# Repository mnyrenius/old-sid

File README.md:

# old-sid
Old project using MOS6581/8580

PCB design + software.

## Schematics

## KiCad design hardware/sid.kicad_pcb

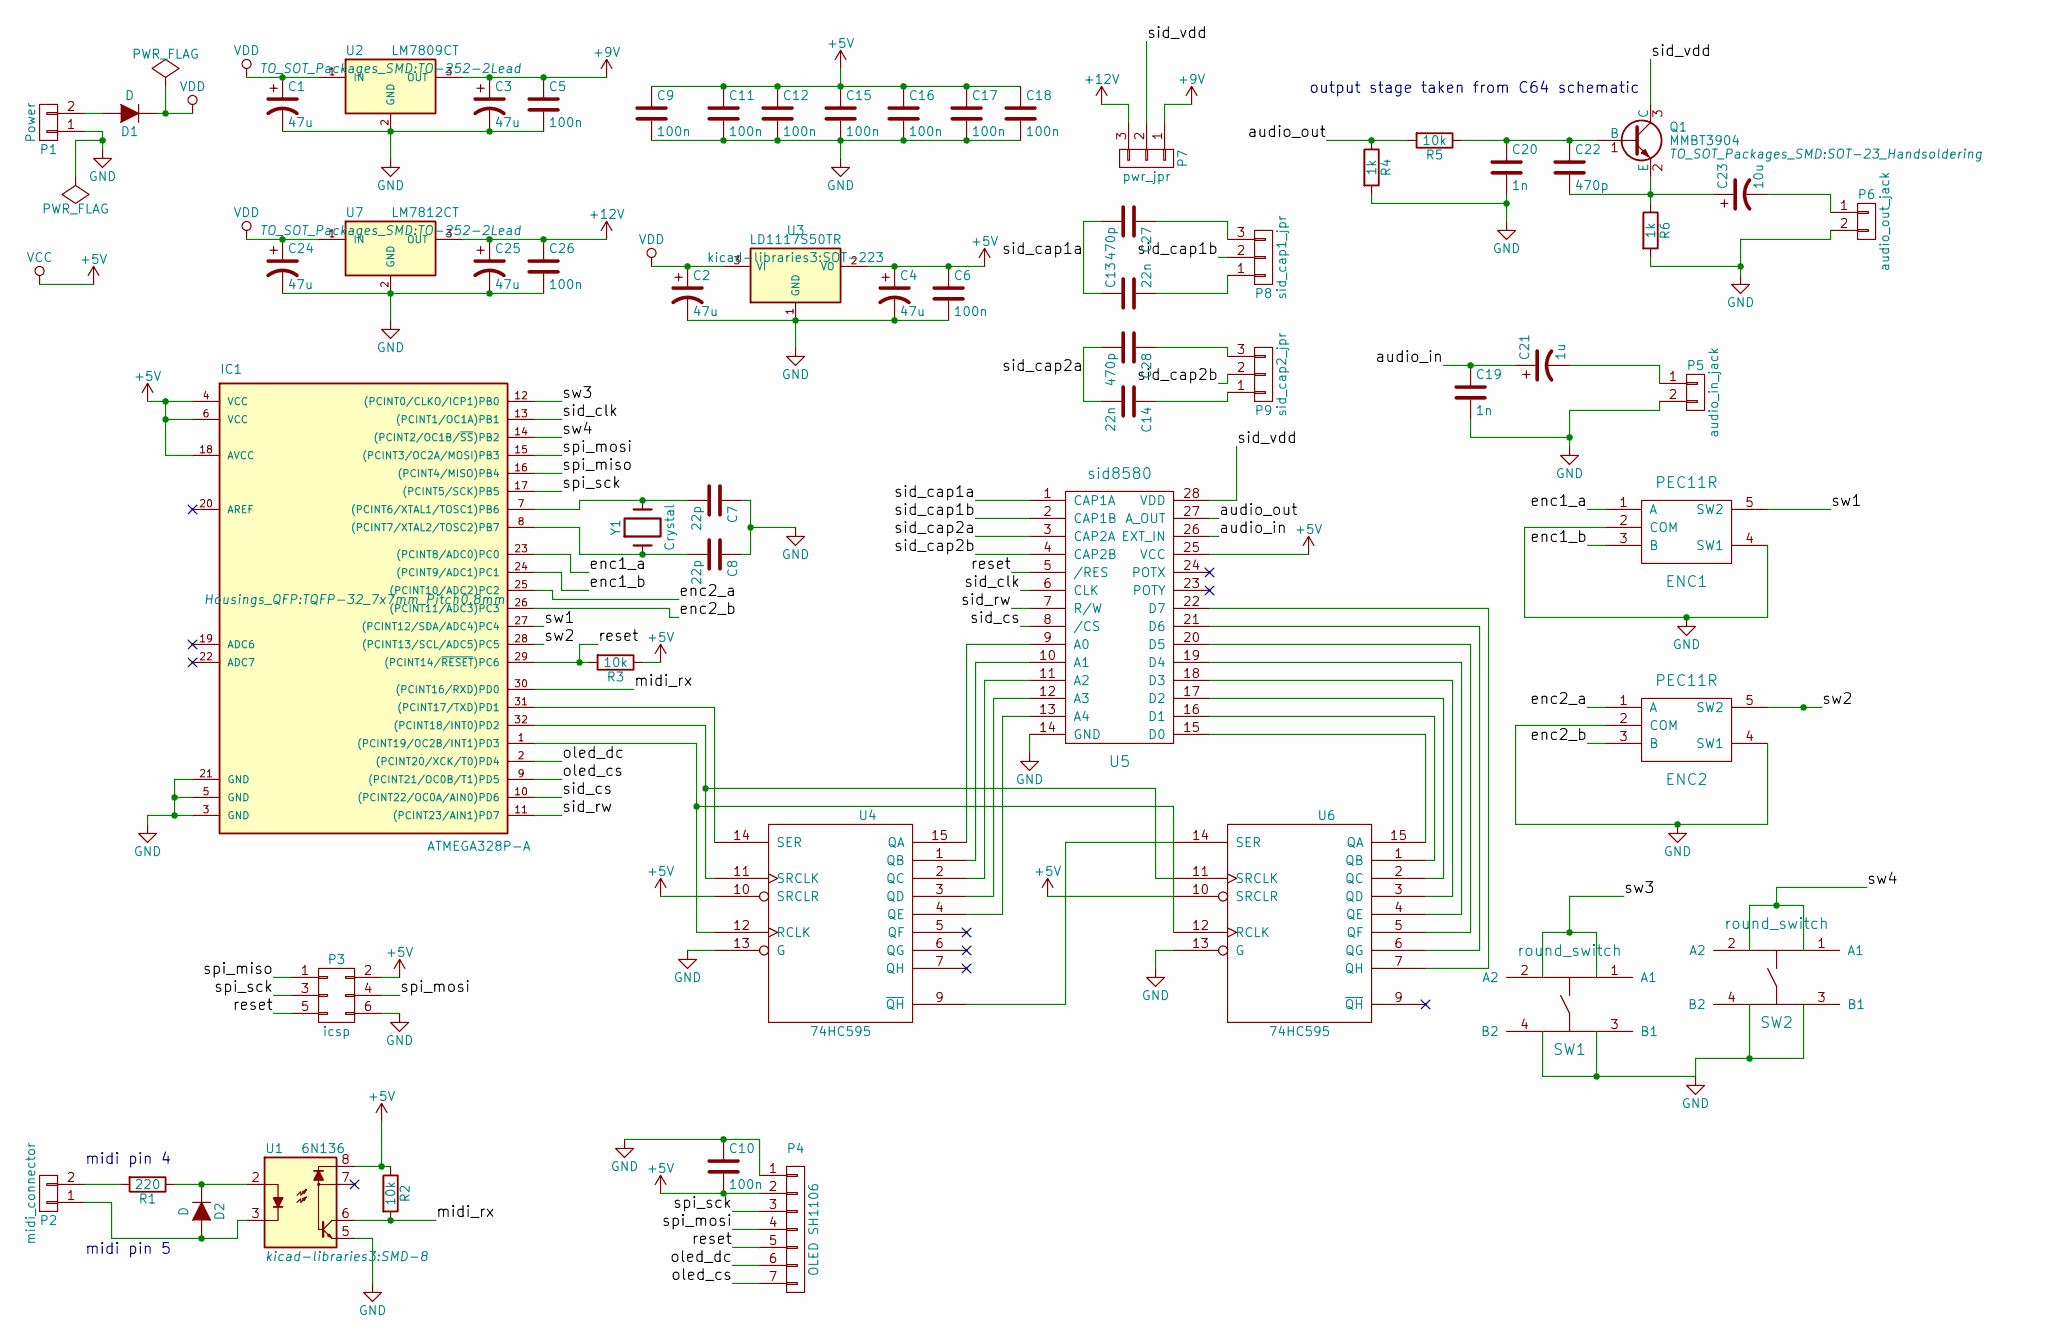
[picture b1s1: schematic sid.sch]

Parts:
C1, C2, C3, C4, C24, C25: 47u; c_elec_4x5.3
C5, C6, C9, C10, C11, C12, C15, C16, C17, C18, C26: 100n; C_0603_HandSoldering
C7, C8: 22p; C_0603_HandSoldering
C13, C14: 22n; C_0603_HandSoldering
C19, C20: 1n; C_0603_HandSoldering
C21: 1u; c_elec_4x5.3
C22, C27, C28: 470p; C_0603_HandSoldering
C23: 10u; c_elec_4x5.3
D1: D; SOD123
D2: D; SOD-323
ENC1, ENC2: PEC11R
IC1: ATMEGA328P-A; TQFP-32_7x7mm_Pitch0.8mm
P1: Power; Pin_Header_Straight_1x02
P2: midi_connector; Pin_Header_Straight_1x02
P3: icsp; Pin_Header_Straight_2x03
P4: OLED SH1106; OLED_SH1106
P5: audio_in_jack; Pin_Header_Straight_1x02
P6: audio_out_jack; Pin_Header_Straight_1x02
P7: pwr_jpr; Pin_Header_Straight_1x03
P8: sid_cap1_jpr; Pin_Header_Straight_1x03
P9: sid_cap2_jpr; Pin_Header_Straight_1x03
Q1: MMBT3904; SOT-23_Handsoldering
R1: 220; R_0603_HandSoldering
R2, R3, R5: 10k; R_0603_HandSoldering
R4, R6: 1k; R_0603_HandSoldering
SW1, SW2: round_switch; SWITCH_CK
U1: 6N136; SMD-8
U2: LM7809CT; TO-252-2Lead
U3: LD1117S50TR; SOT-223
U4, U6: 74HC595; SOIC-16_3.9x9.9mm_Pitch1.27mm
U5: sid8580; DIP-28_W15.24mm_LongPads
U7: LM7812CT; TO-252-2Lead
Y1: Crystal; Crystal_HC49-SD_SMD

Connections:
+5V: C4.1, C6.1, C9.1, C10.2, C11.1, C12.1, C15.1, C16.1, C17.1, C18.1, IC1.4 (VCC), IC1.6 (VCC), IC1.18 (AVCC), P3.2, P4.2, R2.1, R3.1, U1.8, U3.2 (VO), U4.10 (SRCLR), U4.16 (VCC), U5.25 (VCC), U6.10 (SRCLR), U6.16 (VCC)
+9V: C3.1, C5.1, P7.1, U2.3 (OUT)
+12V: C25.1, C26.1, P7.3, U7.3 (OUT)
/audio_in: C19.1, C21.1, U5.26 (EXT_IN)
/audio_out: R4.1, R5.2, U5.27 (A_OUT)
/enc1_a: ENC1.1 (A), IC1.23 ((PCINT8/ADC0)PC0)
/enc1_b: ENC1.3 (B), IC1.24 ((PCINT9/ADC1)PC1)
/enc2_a: ENC2.1 (A), IC1.25 ((PCINT10/ADC2)PC2)
/enc2_b: ENC2.3 (B), IC1.26 ((PCINT11/ADC3)PC3)
/midi_rx: IC1.30 ((PCINT16/RXD)PD0), R2.2, U1.6
/oled_cs: IC1.9 ((PCINT21/OC0B/T1)PD5), P4.7
/oled_dc: IC1.2 ((PCINT20/XCK/T0)PD4), P4.6
/reset: IC1.29 ((PCINT14/~RESET~)PC6), P3.5, P4.5, R3.2, U5.5 (/RES)
/sid_cap1a: C13.1, C27.2, U5.1 (CAP1A)
/sid_cap1b: P8.2, U5.2 (CAP1B)
/sid_cap2a: C14.2, C28.2, U5.3 (CAP2A)
/sid_cap2b: P9.2, U5.4 (CAP2B)
/sid_clk: IC1.13 ((PCINT1/OC1A)PB1), U5.6 (CLK)
/sid_cs: IC1.10 ((PCINT22/OC0A/AIN0)PD6), U5.8 (/CS)
/sid_rw: IC1.11 ((PCINT23/AIN1)PD7), U5.7 (R/W)
/sid_vdd: P7.2, Q1.3 (C), U5.28 (VDD)
/spi_miso: IC1.16 ((PCINT4/MISO)PB4), P3.1
/spi_mosi: IC1.15 ((PCINT3/OC2A/MOSI)PB3), P3.4, P4.4
/spi_sck: IC1.17 ((PCINT5/SCK)PB5), P3.3, P4.3
/sw1: ENC1.5 (SW2), IC1.27 ((PCINT12/SDA/ADC4)PC4)
/sw2: ENC2.5 (SW2), IC1.28 ((PCINT13/SCL/ADC5)PC5)
/sw3: IC1.12 ((PCINT0/CLKO/ICP1)PB0), SW1.1 (A1), SW1.2 (A2)
/sw4: IC1.14 ((PCINT2/OC1B/~SS~)PB2), SW2.1 (A1), SW2.2 (A2)
GND: C1.2, C2.2, C3.2, C4.2, C5.2, C6.2, C7.1, C8.1, C9.2, C10.1, C11.2, C12.2, C15.2, C16.2, C17.2, C18.2, C19.2, C20.2, C24.2, C25.2, C26.2, ENC1.2 (COM), ENC1.4 (SW1), ENC2.2 (COM), ENC2.4 (SW1), IC1.3 (GND), IC1.5 (GND), IC1.21 (GND), P1.1, P3.6, P4.1, P5.2, P6.2, R4.2, R6.2, SW1.3 (B1), SW1.4 (B2), SW2.3 (B1), SW2.4 (B2), U1.5, U2.2 (GND), U3.1 (GND), U4.8 (GND), U4.13 (G), U5.14 (GND), U6.8 (GND), U6.13 (G), U7.2 (GND)
unnamed: C7.2, IC1.7 ((PCINT6/XTAL1/TOSC1)PB6), Y1.2
unnamed: C8.2, IC1.8 ((PCINT7/XTAL2/TOSC2)PB7), Y1.1
unnamed: C13.2, P8.1
unnamed: C14.1, P9.1
unnamed: C20.1, C22.1, Q1.1 (B), R5.1
unnamed: C21.2, P5.1
unnamed: C22.2, C23.1, Q1.2 (E), R6.1
unnamed: C23.2, P6.1
unnamed: C27.1, P8.3
unnamed: C28.1, P9.3
unnamed: D1.2 (A), P1.2
unnamed: D2.1 (K), R1.1, U1.2
unnamed: D2.2 (A), P2.1, U1.3
unnamed: IC1.1 ((PCINT19/OC2B/INT1)PD3), U4.12 (RCLK), U6.12 (RCLK)
unnamed: IC1.31 ((PCINT17/TXD)PD1), U4.14 (SER)
unnamed: IC1.32 ((PCINT18/INT0)PD2), U4.11 (SRCLK), U6.11 (SRCLK)
unnamed: P2.2, R1.2
unnamed: U4.1 (QB), U5.10 (A1)
unnamed: U4.2 (QC), U5.11 (A2)
unnamed: U4.3 (QD), U5.12 (A3)
unnamed: U4.4 (QE), U5.13 (A4)
unnamed: U4.9 (~QH), U6.14 (SER)
unnamed: U4.15 (QA), U5.9 (A0)
unnamed: U5.15 (D0), U6.15 (QA)
unnamed: U5.16 (D1), U6.1 (QB)
unnamed: U5.17 (D2), U6.2 (QC)
unnamed: U5.18 (D3), U6.3 (QD)
unnamed: U5.19 (D4), U6.4 (QE)
unnamed: U5.20 (D5), U6.5 (QF)
unnamed: U5.21 (D6), U6.6 (QG)
unnamed: U5.22 (D7), U6.7 (QH)
VDD: C1.1, C2.1, C24.1, D1.1 (K), U2.1 (IN), U3.3 (VI), U7.1 (IN)

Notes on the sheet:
midi pin 4
midi pin 5
output stage taken from C64 schematic

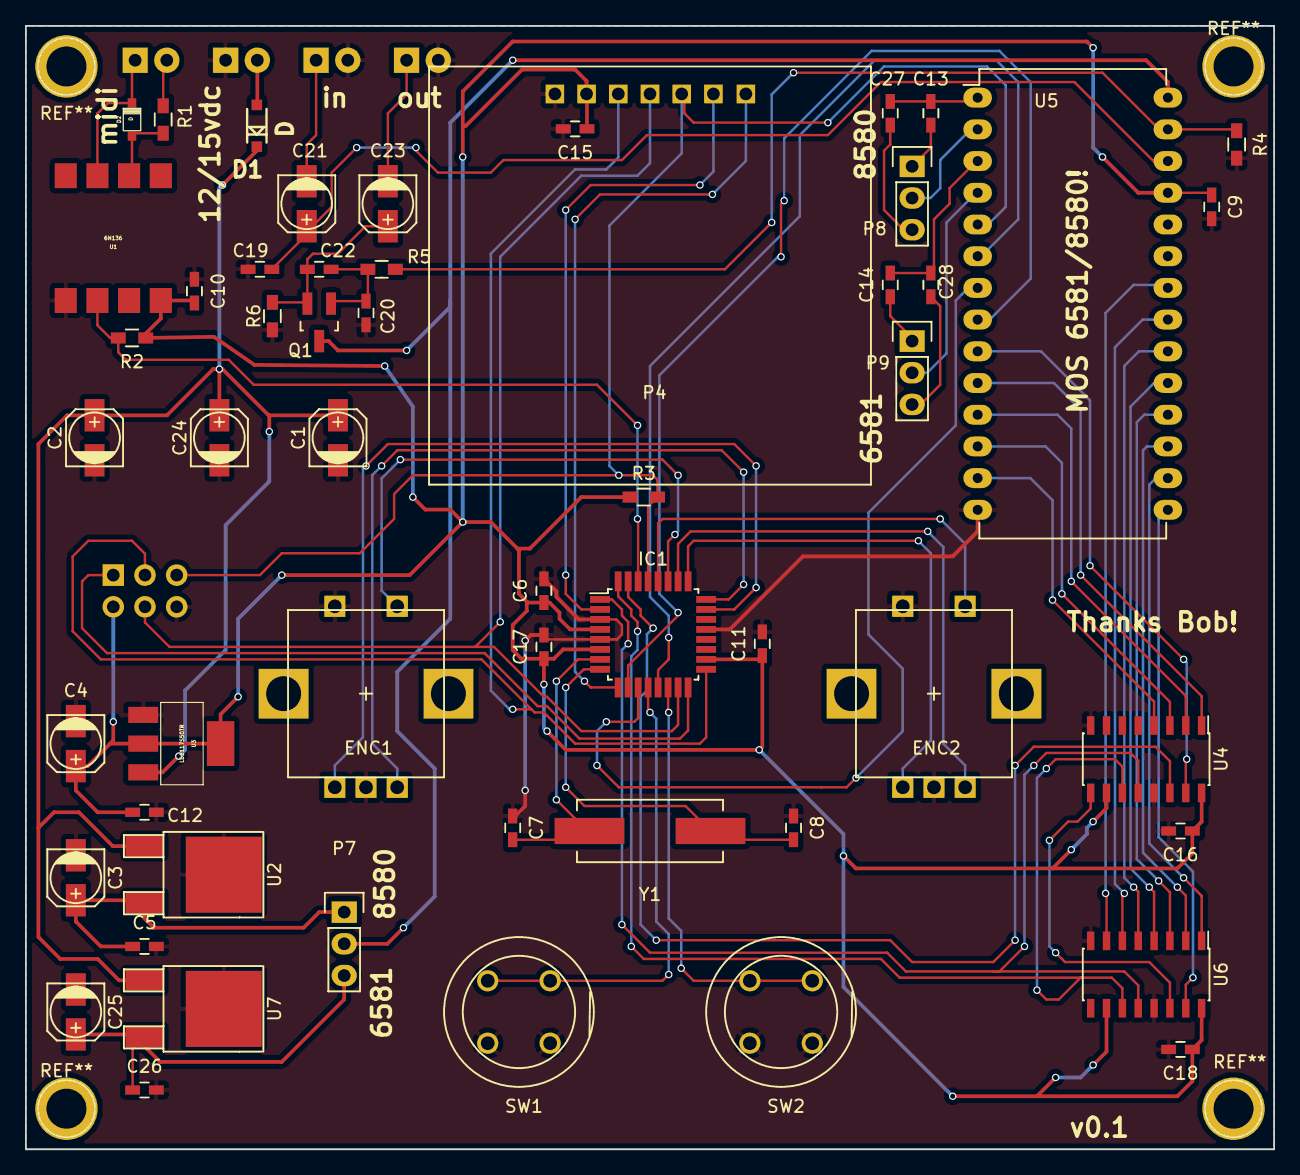
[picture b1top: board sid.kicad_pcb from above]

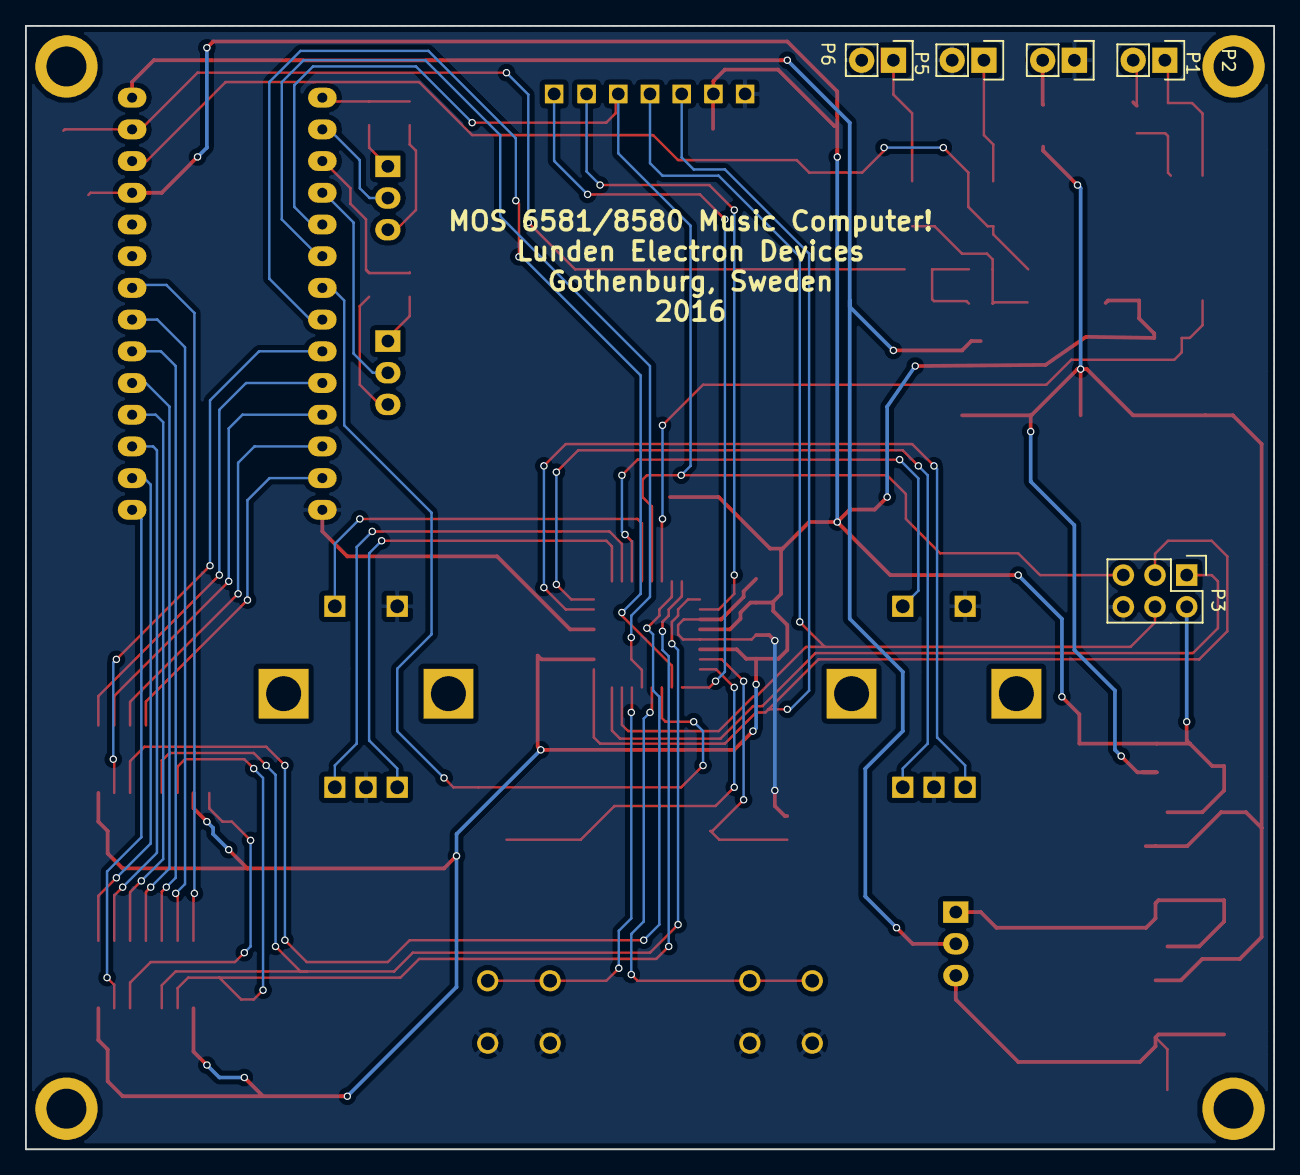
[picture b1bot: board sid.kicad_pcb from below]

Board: 2 copper layers, 100.0 x 90.0 mm, 59 parts (5 on the bottom side), 61 nets.

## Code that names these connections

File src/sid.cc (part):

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 *
 * ------------------------------------ */

const uint8_t midi_rx     = PD0;
const uint8_t hc595_data  = PD1;
const uint8_t hc595_clk   = PD2;
const uint8_t hc595_latch = PD3;

const uint8_t sid_clk     = PB1;
const uint8_t sid_cs      = PD6;
const uint8_t sid_rw      = PD7;
 
const uint8_t spi_mosi    = PB3;
const uint8_t spi_miso    = PB4;
const uint8_t spi_clk     = PB5; 
const uint8_t spi_ss      = PB2; 

const uint8_t enc1_a      = PC0;
const uint8_t enc1_b      = PC1;
const uint8_t enc2_a      = PC2;
const uint8_t enc2_b      = PC3;
const uint8_t sw1         = PC4;
const uint8_t sw2         = PC5;
const uint8_t sw3         = PB0;

const uint16_t notes[] PROGMEM = 
{
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
Menu menu (& voice1_items[0], & render_item, strings::mark);

Encoder _e1 (DDRC, PORTC, PINC, enc1_a, enc1_b, sw1);
Encoder _e2 (DDRC, PORTC, PINC, enc2_a, enc2_b, sw2);
Ui _ui (_e1, _e2, menu, _oled, _settings);
Uart _serial;
Midi<MidiHandler> _midi (_serial); 
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       |  _BV (spi_clk)
       |  _BV (spi_ss)
       |  _BV (sid_clk)
       |  _BV (PD0);

  bit::set (PORTB, sw3);

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
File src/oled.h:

#ifndef _OLED_H_
#define _OLED_H_

#include "avr_types.h"
#include <string.h>
#include <stdlib.h>
#include <avr/pgmspace.h>

const uint8_t ASCII[][5] PROGMEM = 
{
  { 0x00, 0x00, 0x00, 0x00, 0x00 } // 20   (space)
  ,{ 0x00, 0x00, 0x5f, 0x00, 0x00 } // 21 !
  ,{ 0x00, 0x07, 0x00, 0x07, 0x00 } // 22 "
  ,{ 0x14, 0x7f, 0x14, 0x7f, 0x14 } // 23 #
  ,{ 0x24, 0x2a, 0x7f, 0x2a, 0x12 } // 24 $
  ,{ 0x23, 0x13, 0x08, 0x64, 0x62 } // 25 %
  ,{ 0x36, 0x49, 0x55, 0x22, 0x50 } // 26 &
  ,{ 0x00, 0x05, 0x03, 0x00, 0x00 } // 27 '
  ,{ 0x00, 0x1c, 0x22, 0x41, 0x00 } // 28 (
  ,{ 0x00, 0x41, 0x22, 0x1c, 0x00 } // 29 )
  ,{ 0x14, 0x08, 0x3e, 0x08, 0x14 } // 2a *
  ,{ 0x08, 0x08, 0x3e, 0x08, 0x08 } // 2b +
  ,{ 0x00, 0x50, 0x30, 0x00, 0x00 } // 2c ,
  ,{ 0x08, 0x08, 0x08, 0x08, 0x08 } // 2d -
  ,{ 0x00, 0x60, 0x60, 0x00, 0x00 } // 2e .
  ,{ 0x20, 0x10, 0x08, 0x04, 0x02 } // 2f /
  ,{ 0x3e, 0x51, 0x49, 0x45, 0x3e } // 30 0
  ,{ 0x00, 0x42, 0x7f, 0x40, 0x00 } // 31 1
  ,{ 0x42, 0x61, 0x51, 0x49, 0x46 } // 32 2
  ,{ 0x21, 0x41, 0x45, 0x4b, 0x31 } // 33 3
  ,{ 0x18, 0x14, 0x12, 0x7f, 0x10 } // 34 4
  ,{ 0x27, 0x45, 0x45, 0x45, 0x39 } // 35 5
  ,{ 0x3c, 0x4a, 0x49, 0x49, 0x30 } // 36 6
  ,{ 0x01, 0x71, 0x09, 0x05, 0x03 } // 37 7
  ,{ 0x36, 0x49, 0x49, 0x49, 0x36 } // 38 8
  ,{ 0x06, 0x49, 0x49, 0x29, 0x1e } // 39 9
  ,{ 0x00, 0x36, 0x36, 0x00, 0x00 } // 3a :
  ,{ 0x00, 0x56, 0x36, 0x00, 0x00 } // 3b ;
  ,{ 0x08, 0x14, 0x22, 0x41, 0x00 } // 3c <
  ,{ 0x14, 0x14, 0x14, 0x14, 0x14 } // 3d =
  ,{ 0x00, 0x41, 0x22, 0x14, 0x08 } // 3e >
  ,{ 0x02, 0x01, 0x51, 0x09, 0x06 } // 3f ?
  ,{ 0x32, 0x49, 0x79, 0x41, 0x3e } // 40 @
  ,{ 0x7e, 0x11, 0x11, 0x11, 0x7e } // 41 A
  ,{ 0x7f, 0x49, 0x49, 0x49, 0x36 } // 42 B
  ,{ 0x3e, 0x41, 0x41, 0x41, 0x22 } // 43 C
  ,{ 0x7f, 0x41, 0x41, 0x22, 0x1c } // 44 D
  ,{ 0x7f, 0x49, 0x49, 0x49, 0x41 } // 45 E
  ,{ 0x7f, 0x09, 0x09, 0x09, 0x01 } // 46 F
  ,{ 0x3e, 0x41, 0x49, 0x49, 0x7a } // 47 G
  ,{ 0x7f, 0x08, 0x08, 0x08, 0x7f } // 48 H
  ,{ 0x00, 0x41, 0x7f, 0x41, 0x00 } // 49 I
  ,{ 0x20, 0x40, 0x41, 0x3f, 0x01 } // 4a J
  ,{ 0x7f, 0x08, 0x14, 0x22, 0x41 } // 4b K
  ,{ 0x7f, 0x40, 0x40, 0x40, 0x40 } // 4c L
  ,{ 0x7f, 0x02, 0x0c, 0x02, 0x7f } // 4d M
  ,{ 0x7f, 0x04, 0x08, 0x10, 0x7f } // 4e N
  ,{ 0x3e, 0x41, 0x41, 0x41, 0x3e } // 4f O
  ,{ 0x7f, 0x09, 0x09, 0x09, 0x06 } // 50 P
  ,{ 0x3e, 0x41, 0x51, 0x21, 0x5e } // 51 Q
  ,{ 0x7f, 0x09, 0x19, 0x29, 0x46 } // 52 R
  ,{ 0x46, 0x49, 0x49, 0x49, 0x31 } // 53 S
  ,{ 0x01, 0x01, 0x7f, 0x01, 0x01 } // 54 T
  ,{ 0x3f, 0x40, 0x40, 0x40, 0x3f } // 55 U
  ,{ 0x1f, 0x20, 0x40, 0x20, 0x1f } // 56 V
  ,{ 0x3f, 0x40, 0x38, 0x40, 0x3f } // 57 W
  ,{ 0x63, 0x14, 0x08, 0x14, 0x63 } // 58 X
  ,{ 0x07, 0x08, 0x70, 0x08, 0x07 } // 59 Y
  ,{ 0x61, 0x51, 0x49, 0x45, 0x43 } // 5a Z
  ,{ 0x00, 0x7f, 0x41, 0x41, 0x00 } // 5b [
  ,{ 0x02, 0x04, 0x08, 0x10, 0x20 } // 5c backslash
  ,{ 0x00, 0x41, 0x41, 0x7f, 0x00 } // 5d ]
  ,{ 0x04, 0x02, 0x01, 0x02, 0x04 } // 5e ^
  ,{ 0x40, 0x40, 0x40, 0x40, 0x40 } // 5f _
  ,{ 0x00, 0x01, 0x02, 0x04, 0x00 } // 60 `
  ,{ 0x20, 0x54, 0x54, 0x54, 0x78 } // 61 a
  ,{ 0x7f, 0x48, 0x44, 0x44, 0x38 } // 62 b
  ,{ 0x38, 0x44, 0x44, 0x44, 0x20 } // 63 c
  ,{ 0x38, 0x44, 0x44, 0x48, 0x7f } // 64 d
  ,{ 0x38, 0x54, 0x54, 0x54, 0x18 } // 65 e
  ,{ 0x08, 0x7e, 0x09, 0x01, 0x02 } // 66 f
  ,{ 0x0c, 0x52, 0x52, 0x52, 0x3e } // 67 g
  ,{ 0x7f, 0x08, 0x04, 0x04, 0x78 } // 68 h
  ,{ 0x00, 0x44, 0x7d, 0x40, 0x00 } // 69 i
  ,{ 0x20, 0x40, 0x44, 0x3d, 0x00 } // 6a j 
  ,{ 0x7f, 0x10, 0x28, 0x44, 0x00 } // 6b k
  ,{ 0x00, 0x41, 0x7f, 0x40, 0x00 } // 6c l
  ,{ 0x7c, 0x04, 0x18, 0x04, 0x78 } // 6d m
  ,{ 0x7c, 0x08, 0x04, 0x04, 0x78 } // 6e n
  ,{ 0x38, 0x44, 0x44, 0x44, 0x38 } // 6f o
  ,{ 0x7c, 0x14, 0x14, 0x14, 0x08 } // 70 p
  ,{ 0x08, 0x14, 0x14, 0x18, 0x7c } // 71 q
  ,{ 0x7c, 0x08, 0x04, 0x04, 0x08 } // 72 r
  ,{ 0x48, 0x54, 0x54, 0x54, 0x20 } // 73 s
  ,{ 0x04, 0x3f, 0x44, 0x40, 0x20 } // 74 t
  ,{ 0x3c, 0x40, 0x40, 0x20, 0x7c } // 75 u
  ,{ 0x1c, 0x20, 0x40, 0x20, 0x1c } // 76 v
  ,{ 0x3c, 0x40, 0x30, 0x40, 0x3c } // 77 w
  ,{ 0x44, 0x28, 0x10, 0x28, 0x44 } // 78 x
  ,{ 0x0c, 0x50, 0x50, 0x50, 0x3c } // 79 y
  ,{ 0x44, 0x64, 0x54, 0x4c, 0x44 } // 7a z
  ,{ 0x00, 0x08, 0x36, 0x41, 0x00 } // 7b {
  ,{ 0x00, 0x00, 0x7f, 0x00, 0x00 } // 7c |
  ,{ 0x00, 0x41, 0x36, 0x08, 0x00 } // 7d }
,{ 0x10, 0x08, 0x08, 0x10, 0x08 } // 7e ~
,{ 0x78, 0x46, 0x41, 0x46, 0x78 } // 7f DEL
}; 
   
const uint8_t oled_dc     = PD4;
const uint8_t oled_cs     = PD5;

struct Device
{
  static void spi_transfer (uint8_t dc, uint8_t data)
  {
    if (dc == 0)
    {
      bit::clear (PORTD, oled_dc);
    }

    else
    {
      bit::set (PORTD, oled_dc);
    }

    bit::clear (PORTD, oled_cs);

    SPDR = data;
    while (!(SPSR & (1 << SPIF)));

    bit::set (PORTD, oled_cs);
  }

  static void command (uint8_t command)
  {
    spi_transfer (0, command);
  }

  static void data (uint8_t data)
  {
    spi_transfer (1, data);
  }
};  

class Oled
{
  public:
    Oled ()
    {
      //memset (_screen, 0, 128);
    }

    ~Oled ()
    {
    }

    void init ()
    {
      Device::command (0x0ae);       
      Device::command (0x0d5);
      Device::command (0x080);
      Device::command (0x0a8);
      Device::command (0x03f);
      Device::command (0x0d3);
      Device::command (0x000);
      Device::command (0x040);       
      Device::command (0x08d);
      Device::command (0x014);
      Device::command (0x020);
      Device::command (0x000);
      Device::command (0x0a1);       
      Device::command (0x0c8);       
      Device::command (0x0da);
      Device::command (0x012);
      Device::command (0x081);
      Device::command (0x0cf);
      Device::command (0x0d9);
      Device::command (0x0f1);
      Device::command (0x0db);
      Device::command (0x040);
      Device::command (0x02e);       
      Device::command (0x0a4);       
      Device::command (0x0a6);
    }

    void off ()
    {
      Device::command (0x0ae);       
    }

    void on ()
    {
      Device::command (0x0af);     
    }

    void clear ()
    {
      for (uint8_t page = 0; page < 64/8; page++) 
      {
        for (uint8_t col = 2; col < 130; col++) 
        {
          Device::command(0xb0 + page);
          Device::command(col & 0xf);
          Device::command(0x10 | (col >> 4));
          Device::data (0);
        }
      } 

      //memset (_screen, 0, 128);
    }

    void set_contrast (uint8_t contrast)
    {
    }

    void write_text (uint8_t x, uint8_t y, const char * text, uint8_t len, bool inverted = false)
    {
      uint8_t col = x;
      uint8_t buffer[5];

      for (uint8_t i = 0; i < len; ++i) 
      {
        memcpy_P (buffer, ASCII[text[i] - 0x20], 5);
        Device::command(0xb0 + y);
        Device::command(col & 0xf);
        Device::command(0x10 | (col >> 4));

        if (inverted)
        { 
          Device::data (~buffer[0]);
          Device::data (~buffer[1]);
          Device::data (~buffer[2]);
          Device::data (~buffer[3]);
          Device::data (~buffer[4]);
          Device::data (0xff);
        }

        else
        {
          Device::data (buffer[0]);
          Device::data (buffer[1]);
          Device::data (buffer[2]);
          Device::data (buffer[3]);
          Device::data (buffer[4]);
          Device::data (0);
        }

        col += 6;
      } 
      /*
      for (int i = 0; i < len; ++i)
      {
        memcpy_P (_screen + x + (i * 6) + y * 128, ASCII[text[i] - 0x20], 5);
      }
      */
    }

    /*
    template<int N>
    void write_text (uint8_t x, uint8_t y, const char (&text)[N], bool inverted = false)
    {
      write_text (x, y, text, N, inverted);
      Device::command(0xb0 + 0);
      Device::command(col & 0xf);
      Device::command(0x10 | (col >> 4));
      Device::data (ASCII['N'][0]); 
      Device::data (ASCII['N'][1]); 
      Device::data (ASCII['N'][2]); 
      Device::data (ASCII['N'][3]); 
      Device::data (ASCII['N'][4]);
    } 
*/

    void write_text (uint8_t x, uint8_t y, const char * text, bool inverted = false)
    {
      write_text (x, y, text, strlen (text), inverted);
    }

    void write_number (uint8_t x, uint8_t y, int16_t n)
    {
      char buffer[5];
      itoa (n, buffer, 10);
      write_text (x, y, buffer);
    }

    void render ()
    {
      /*
      for (uint8_t page = 0; page < 64/8; page++) 
      {
        for (uint8_t col = 2; col < 130; col++) 
        {
          Device::command(0xb0 + page);
          Device::command(col & 0xf);
          Device::command(0x10 | (col >> 4));
          Device::data (_screen[col - 2 + page * 128]);
        }
      } 
      */
    }

  private:
    atm8::pin _dc;
    atm8::pin _cs;
};

#endif /* _OLED_H_ */

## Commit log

2020-12-23 Copied files from old repo
2020-12-23 Add schematics svg
